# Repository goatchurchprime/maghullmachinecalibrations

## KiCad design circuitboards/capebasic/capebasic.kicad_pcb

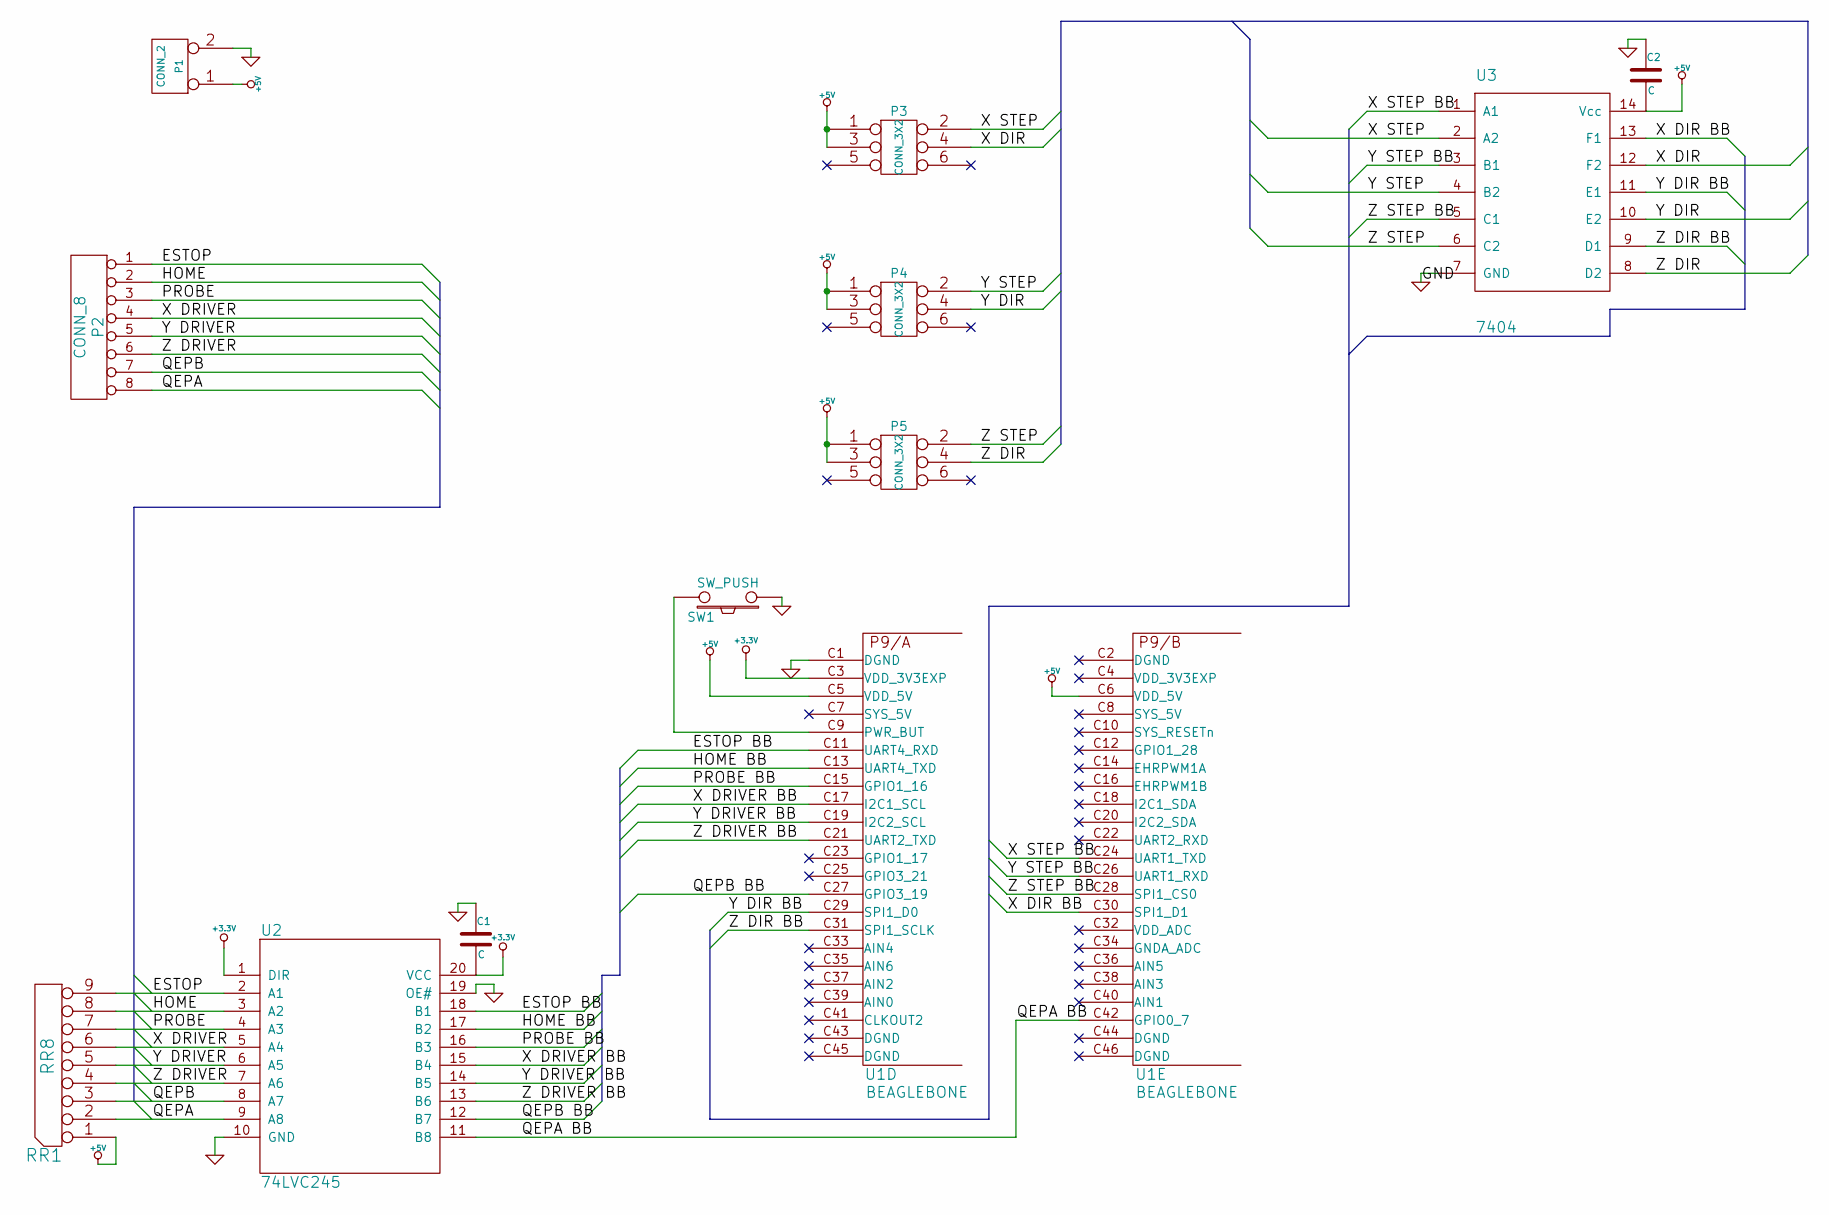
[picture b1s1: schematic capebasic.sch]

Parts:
C1, C2: C
P1: CONN_2
P2: CONN_8
P3, P4, P5: CONN_3X2
RR1: RR8
SW1: SW_PUSH
U1: BEAGLEBONE
U2: 74LVC245
U3: 7404

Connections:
+3.3V: C1.2, U1.C3 (VDD_3V3EXP), U2.1 (DIR), U2.20 (VCC)
+5V: C2.2, P1.1, P3.1, P3.3, P4.1, P4.3, P5.1, P5.3, RR1.1 (COM), U1.C5 (VDD_5V), U1.C6 (VDD_5V), U3.14 (Vcc)
/ESTOP: P2.1, RR1.9, U2.2 (A1)
/ESTOP BB: U1.C11 (UART4_RXD), U2.18 (B1)
/HOME: P2.2, RR1.8, U2.3 (A2)
/HOME BB: U1.C13 (UART4_TXD), U2.17 (B2)
/PROBE: P2.3, RR1.7, U2.4 (A3)
/PROBE BB: U1.C15 (GPIO1_16), U2.16 (B3)
/QEPA: P2.8, RR1.2, U2.9 (A8)
/QEPA BB: U1.C42 (GPIO0_7), U2.11 (B8)
/QEPB: P2.7, RR1.3, U2.8 (A7)
/QEPB BB: U1.C27 (GPIO3_19), U2.12 (B7)
/X DIR: P3.4, U3.12 (F2)
/X DIR BB: U1.C30 (SPI1_D1), U3.13 (F1)
/X DRIVER: P2.4, RR1.6, U2.5 (A4)
/X DRIVER BB: U1.C17 (I2C1_SCL), U2.15 (B4)
/X STEP: P3.2, U3.2 (A2)
/X STEP BB: U1.C24 (UART1_TXD), U3.1 (A1)
/Y DIR: P4.4, U3.10 (E2)
/Y DIR BB: U1.C29 (SPI1_D0), U3.11 (E1)
/Y DRIVER: P2.5, RR1.5, U2.6 (A5)
/Y DRIVER BB: U1.C19 (I2C2_SCL), U2.14 (B5)
/Y STEP: P4.2, U3.4 (B2)
/Y STEP BB: U1.C26 (UART1_RXD), U3.3 (B1)
/Z DIR: P5.4, U3.8 (D2)
/Z DIR BB: U1.C31 (SPI1_SCLK), U3.9 (D1)
/Z DRIVER: P2.6, RR1.4, U2.7 (A6)
/Z DRIVER BB: U1.C21 (UART2_TXD), U2.13 (B6)
/Z STEP: P5.2, U3.6 (C2)
/Z STEP BB: U1.C28 (SPI1_CS0), U3.5 (C1)
GND: C1.1, C2.1, P1.2 (PM), SW1.1, U1.C1 (DGND), U2.10 (GND), U2.19 (OE#), U3.7 (GND)
unnamed: SW1.2, U1.C9 (PWR_BUT)

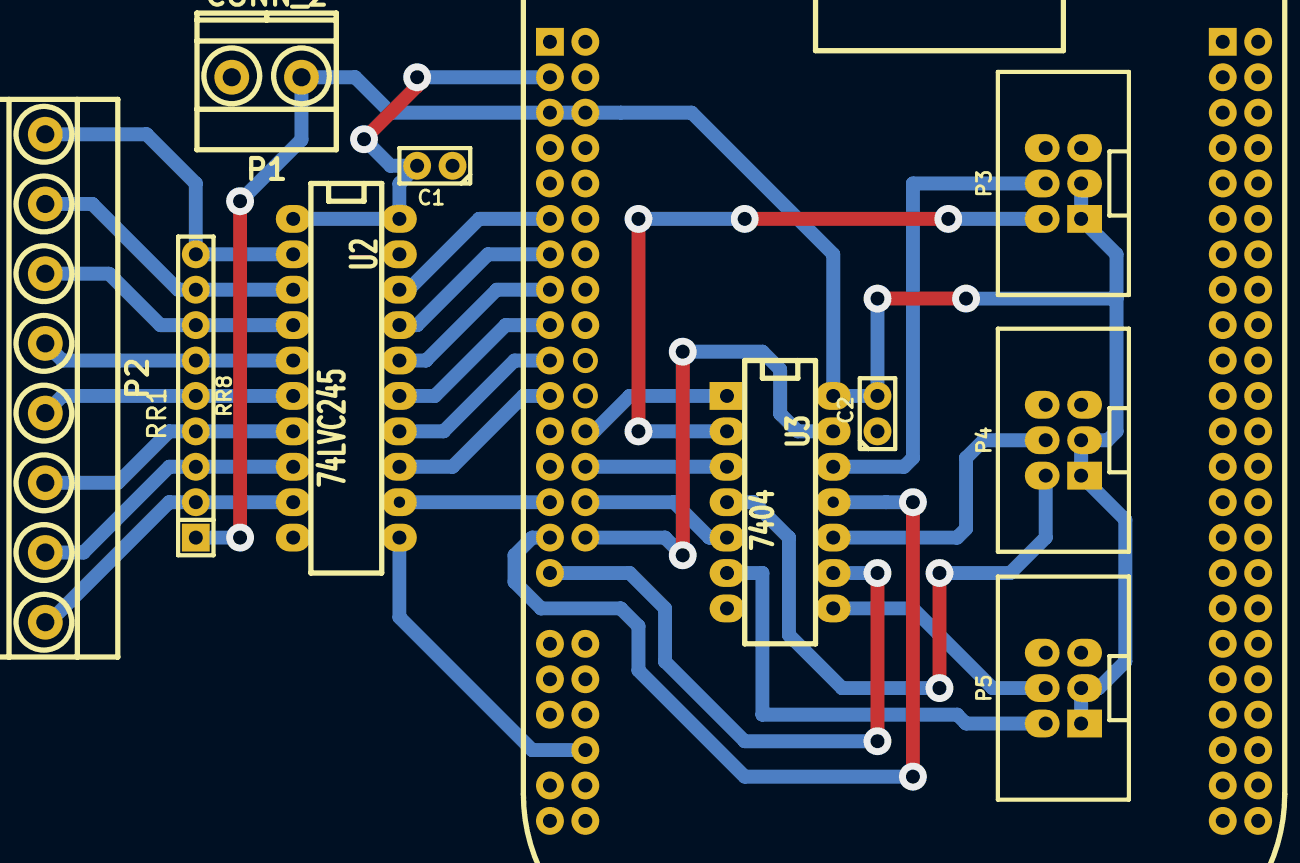
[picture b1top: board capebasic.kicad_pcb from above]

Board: 2 copper layers, 11 parts (0 on the bottom side), 31 nets.

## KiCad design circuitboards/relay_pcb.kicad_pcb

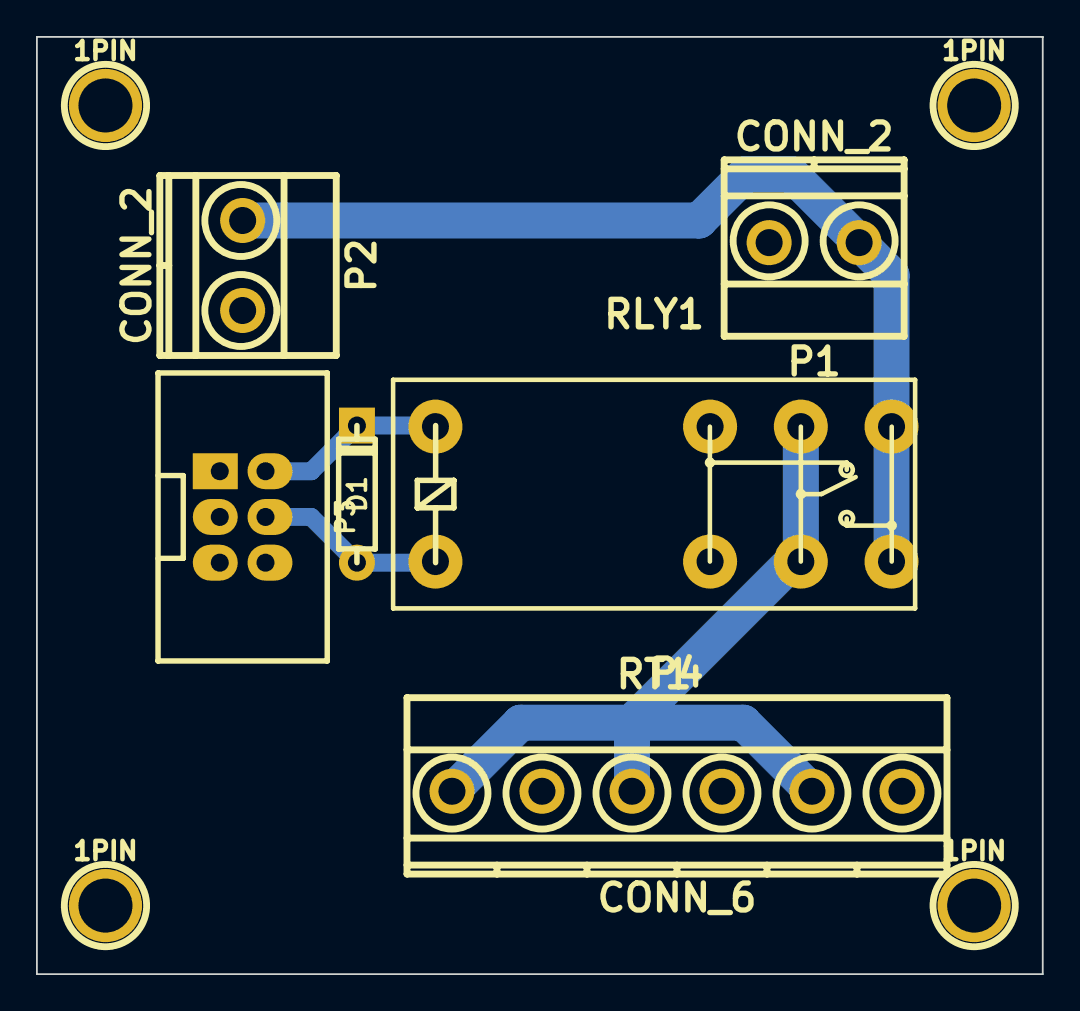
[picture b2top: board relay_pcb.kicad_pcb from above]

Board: 2 copper layers, 55.9 x 52.1 mm, 10 parts (0 on the bottom side), 5 nets.

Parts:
1PIN, 1PIN#2, 1PIN#3, 1PIN#4: P***; 1pin
D1: DIODE; D3
P1, P2: CONN_2; mkds_1,5-2
P3: CONN_3X2; vasch_strip_3x2
P4: CONN_6; mkds_1,5-6
RLY1: RT1; relay_RT1

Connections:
unnamed: D1.1, P3.4, RLY1.1
unnamed: D1.2, P3.2, RLY1.2
unnamed: P4.1, P4.3, P4.5, RLY1.11
unnamed: P1.1, P2.1, RLY1.14
unnamed: 1PIN.1, 1PIN#2.1, 1PIN#3.1, 1PIN#4.1, P1.2, P2.2, P4.2, P4.4, P4.6

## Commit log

2015-04-29 first commit of group of files used in the triangle machine settings and calibrations
2015-04-29 calibration code kind of working for now
2015-04-29 account for inner circle going outwards
2015-04-29 radrg function to give a better display of radius error
2015-05-01 add in print of #define default lines
2015-05-06 put in tblx and armx offsets into the optimization calculation
2015-05-22 add in diagrams explaining the geometry of the machine and the equations
2015-05-28 more recent ncg calibration files
2015-05-29 hacking of code into new form
2015-06-01 made calibration2 shorter and for straight edges
2015-06-01 as far as calibration goes for now with straight edges and forcing the 745 lengths
2015-07-13 half baked direct calculations for the doesmachinemodel
2015-07-14 written and done the dowel 11 dowel holes and 20 measurements
2015-10-05 update the kinematics file
2015-11-10 Added the mk7 beaglebone files
2015-11-18 Add circuitboards directory with pcb3 gbr files
2015-11-18 Add relay_pcb kicad data
2015-11-19 Move relay_pcb stuff to own directory
2015-12-09 Add in all circuit board gbr files
2015-12-09 Add scrap code relating to calibration generation
2015-12-09 Add beaglebone pru experiments code
2015-12-10 Add all necessary files and instructions to build from scratch and move unnecessary files into junk directory
2015-12-10 Add pru experiments code
2016-02-26 pruaccessiblepinouts created online with Bitbucket
2016-03-11 Copy across the logging mk6skins.c file
2016-03-11 Add gerbertocutfiles that convert the circuit diagram files
2016-08-03 added capebasic kicad project folder
2016-08-09 added beaglebone pinout
